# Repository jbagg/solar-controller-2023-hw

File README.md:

This is a differential temperature controller with 8 temperature sensor inputs, 4 digital inputs and 8 opto coupled solid state relay outputs.  The controller is compatible with the [LMT01](https://www.ti.com/product/LMT01) temperature sensor.  Each temperature sensor is connected to the controller with one pair of a cat 5 or 6 cable.  The temperature sensor uses the same 2 wires for both power and signaling.  Each temperature sensor has a max length of 45 meters.

The LMT01 is an ideal temperature sensor for differential temperature controllers as it

* uses digital signaling so no noise is added to the measurement over the cable back to the controller.
* allows for differential signaling for long cables.
* needs only 2 wires (twisted pair) per sensor.  Power and signaling is done over the same wires.

### Sensor Operation

The LMT01 uses a Pulse Train Interface to communicate the temperature where the number of output pulses is proportional to temperature.  The 1 or 0, high or low of each pulse is communicated by switching the device current consumption between two values, aprox 34uA and 125uA.

The controller measures each LMT01 sensor one at a time via U1, ADG707 differential 8-to-1 multiplexer.  When a sensor is muxed, its positive pin is connected to a 3.3kΩ pull up (R17) and its negative pin is connected to a 3.3kΩ pull down (R18).  Each resistor sees about a 300mV change in voltage between the pulse’s high / low 34uA and 125uA change in device current.  When R17’s change is positive, R18’s is negative.  These signal pulses are AC coupled to a differential op-amp circuit (U3A) via C20 and C39.  680pF was chosen to be about half the time constant for the 88Khz pulse.

1 / 88Khz = 11.4uS.  680pF * 10K = 6.8uS.

C20 and C39 must charge before they pass the pulses.  Too large a value looses pulses at the beginning.  680pF was measured to loose about 1 pulse, or about 0.1 C.

The differential op-amp circuit separates common noise from the differential signal that the twisted pair has picked up from noise sources over it’s length.  The differential op-amp circuit has gain to compensate for the signal loss in the cable.  The differential op-amp circuit has a gain of about 5 which is the max value not to saturate the strongest signal, a sensor connected directly to the controller without a length of wire.

[300mV - (-300mV)] * 5 <br>
= 600mV * 5 <br>
= 3v  (U1 has 3.3v supply)

The gain can be increased to just below the saturation point of the shortest cable.  C1 and C2 filter high frequency noise.  The output of the differential op-amp circuit is feed to a comparator with hysteresis (U3B).

The comparator has a hysteresis of 314mV.  A cat-5 twisted pair of up to 45 meters still had enough margin above the 314mV hysteresis for reliable operation.  The output of the comparator is feed to the microcontroller’s external timer counter clock input.

The microcontroller’s external timer counter clock (TCLK0) input feeds both TC0 and TC1 timer counters in the SAM4S2 mcu.  TC0 uses TCLK0 as a clock source and thus counts the pulses from the sensor.  The value of TC0 can be read and converted to a temperature.  TC1 is used to trigger when the LMT01 has finished sending pulses.  TC1 is clocked from the main mcu clock.  TC1 is configured so that its value is reset each time there is an edge on TCLK0.  TC1 compare C register is configured to a value about 2x the normal pulse period of the LMT01.  Each pulse from the LMT01 resets the count in TC1.  When the LMT01 stops sending pulses, TC1’s value grows to match compare C register which triggers an interrupt for the software to read TC0 and then change the mux to the next sensor and start all over again.

### Opto Coupler Ouptputs

Opto coupler AQH0213 is used to drive the coil of a relay that controls the load.  The AQH0213 is apart of a family of opto couplers with the same footprint.  The appropriate opto coupler can be chosen to match the voltage and current requirements of the specific relay for the application.

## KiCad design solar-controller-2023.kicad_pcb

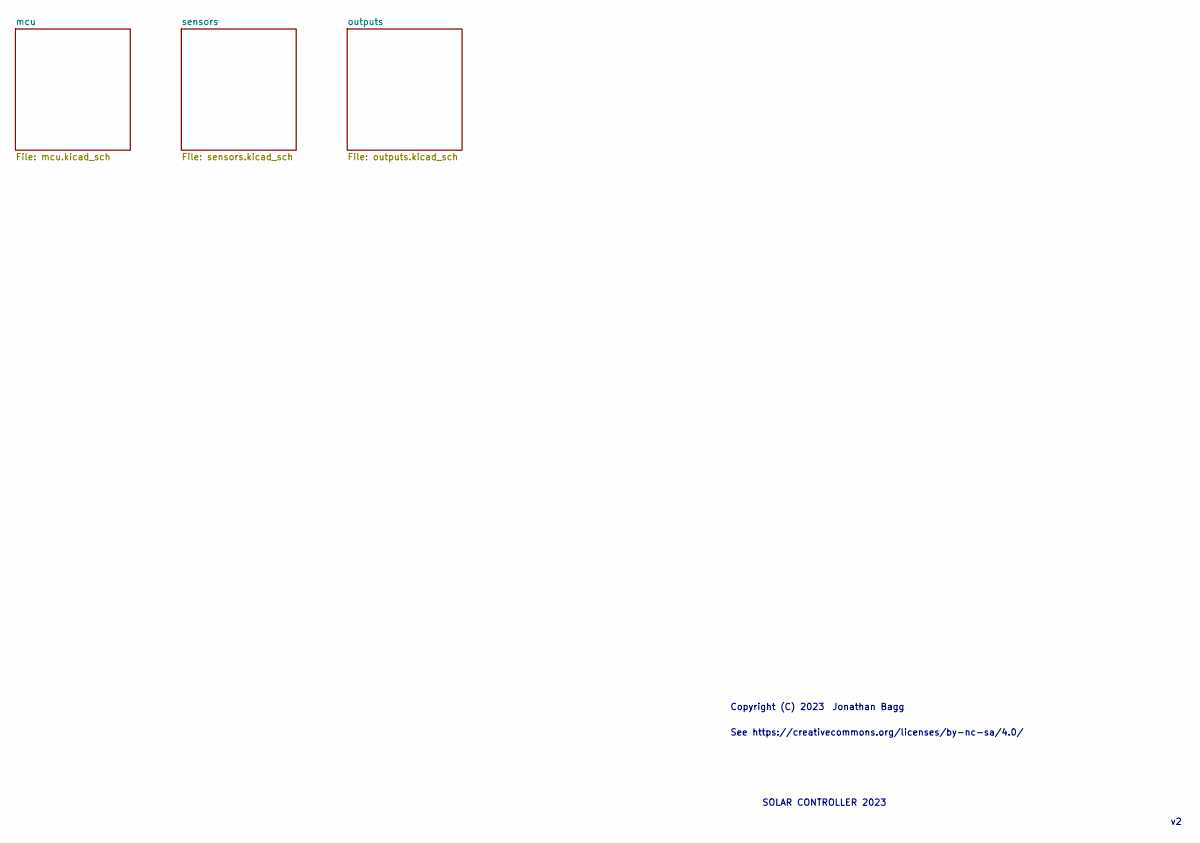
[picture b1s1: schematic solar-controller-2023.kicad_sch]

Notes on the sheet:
Copyright (C) 2023
See https://creativecommons.org/licenses/by-nc-sa/4.0/
Jonathan Bagg
SOLAR CONTROLLER 2023

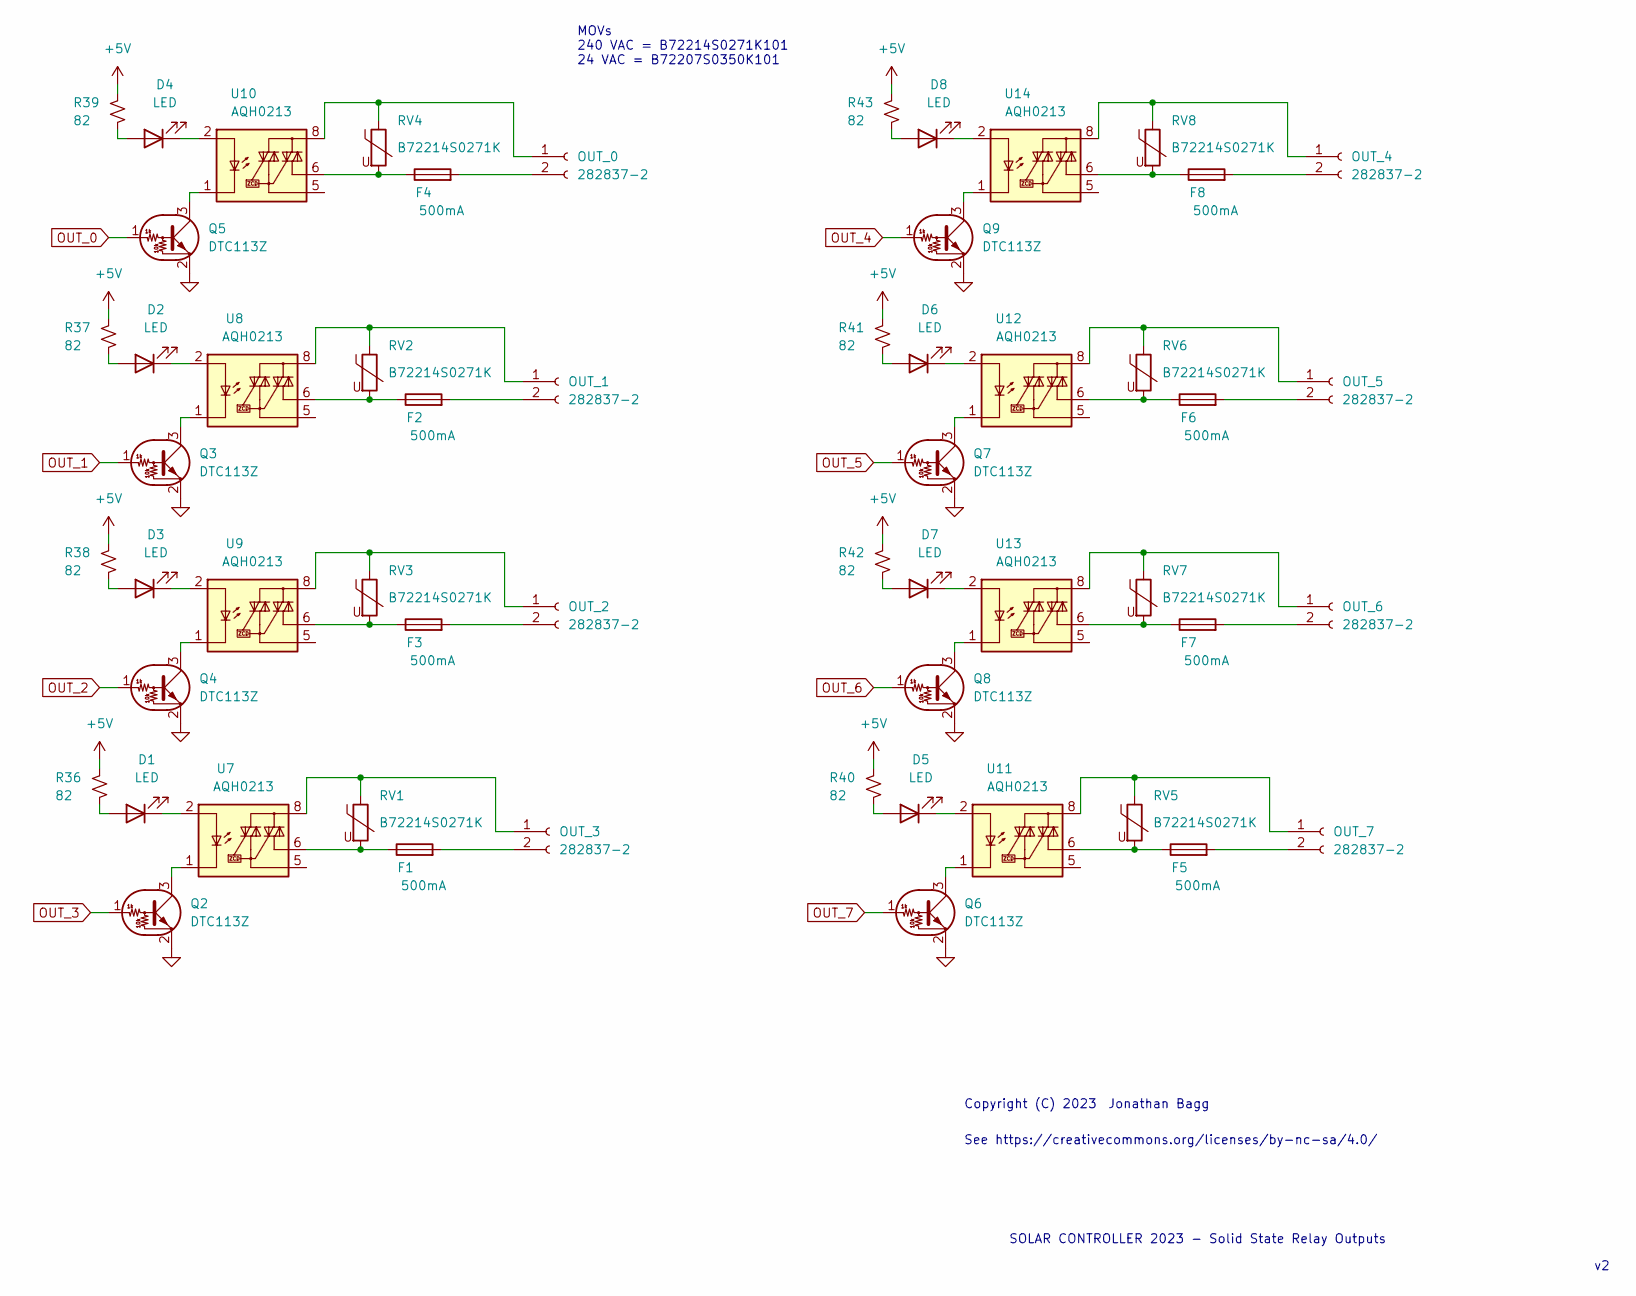
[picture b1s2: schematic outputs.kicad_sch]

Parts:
D1, D2, D3, D4, D5, D6, D7, D8: LED; D_0603_1608Metric_Pad1.05x0.95mm_HandSolder; Digikey 160-1436-1-ND
F1, F2, F3, F4, F5, F6, F7, F8: 500mA; C_Disc_D8.0mm_W5.0mm_P5.00mm; Digikey 507-1924-1-ND
OUT_0, OUT_1, OUT_2, OUT_3, OUT_4, OUT_5, OUT_6, OUT_7: 282837-2; 282837-2_TYC; Digikey A113320-ND
Q2, Q3, Q4, Q5, Q6, Q7, Q8, Q9: DTC113Z; SOT-23
R36, R37, R38, R39, R40, R41, R42, R43: 82; R_0805_2012Metric_Pad1.20x1.40mm_HandSolder; Digikey RMCF0805FT82R0CT-ND
RV1, RV2, RV3, RV4, RV5, RV6, RV7, RV8: B72214S0271K; C_Rect_L9.0mm_W2.5mm_P7.50mm_MKT; Digikey 495-1412-ND
U7, U8, U9, U10, U11, U12, U13, U14: AQH0213; DIP-8-N7_W7.62mm; Digikey 255-5987-ND

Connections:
+5V: R36.1, R37.1, R38.1, R39.1, R40.1, R41.1, R42.1, R43.1; also elsewhere on the board
GND: Q2.2 (E), Q3.2 (E), Q4.2 (E), Q5.2 (E), Q6.2 (E), Q7.2 (E), Q8.2 (E), Q9.2 (E); also elsewhere on the board
unnamed: D1.1 (K), U7.2
unnamed: D1.2 (A), R36.2
unnamed: D2.1 (K), U8.2
unnamed: D2.2 (A), R37.2
unnamed: D3.1 (K), U9.2
unnamed: D3.2 (A), R38.2
unnamed: D4.1 (K), U10.2
unnamed: D4.2 (A), R39.2
unnamed: D5.1 (K), U11.2
unnamed: D5.2 (A), R40.2
unnamed: D6.1 (K), U12.2
unnamed: D6.2 (A), R41.2
unnamed: D7.1 (K), U13.2
unnamed: D7.2 (A), R42.2
unnamed: D8.1 (K), U14.2
unnamed: D8.2 (A), R43.2
unnamed: F1.1, RV1.2, U7.6
unnamed: F1.2, OUT_3.2
unnamed: F2.1, RV2.2, U8.6
unnamed: F2.2, OUT_1.2
unnamed: F3.1, RV3.2, U9.6
unnamed: F3.2, OUT_2.2
unnamed: F4.1, RV4.2, U10.6
unnamed: F4.2, OUT_0.2
unnamed: F5.1, RV5.2, U11.6
unnamed: F5.2, OUT_7.2
unnamed: F6.1, RV6.2, U12.6
unnamed: F6.2, OUT_5.2
unnamed: F7.1, RV7.2, U13.6
unnamed: F7.2, OUT_6.2
unnamed: F8.1, RV8.2, U14.6
unnamed: F8.2, OUT_4.2
unnamed: OUT_0.1, RV4.1, U10.8
unnamed: OUT_1.1, RV2.1, U8.8
unnamed: OUT_2.1, RV3.1, U9.8
unnamed: OUT_3.1, RV1.1, U7.8
unnamed: OUT_4.1, RV8.1, U14.8
unnamed: OUT_5.1, RV6.1, U12.8
unnamed: OUT_6.1, RV7.1, U13.8
unnamed: OUT_7.1, RV5.1, U11.8
unnamed: Q2.3 (C), U7.1, U7.3, U7.4
unnamed: Q3.3 (C), U8.1, U8.3, U8.4
unnamed: Q4.3 (C), U9.1, U9.3, U9.4
unnamed: Q5.3 (C), U10.1, U10.3, U10.4
unnamed: Q6.3 (C), U11.1, U11.3, U11.4
unnamed: Q7.3 (C), U12.1, U12.3, U12.4
unnamed: Q8.3 (C), U13.1, U13.3, U13.4
unnamed: Q9.3 (C), U14.1, U14.3, U14.4
OUT_0: Q5.1 (B); also elsewhere on the board
OUT_1: Q3.1 (B); also elsewhere on the board
OUT_2: Q4.1 (B); also elsewhere on the board
OUT_3: Q2.1 (B); also elsewhere on the board
OUT_4: Q9.1 (B); also elsewhere on the board
OUT_5: Q7.1 (B); also elsewhere on the board
OUT_6: Q8.1 (B); also elsewhere on the board
OUT_7: Q6.1 (B); also elsewhere on the board

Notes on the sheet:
Copyright (C) 2023
See https://creativecommons.org/licenses/by-nc-sa/4.0/
MOVs 240 VAC = B72214S0271K101 24 VAC = B72207S0350K101
SOLAR CONTROLLER 2023 - Solid State Relay Outputs
Jonathan Bagg

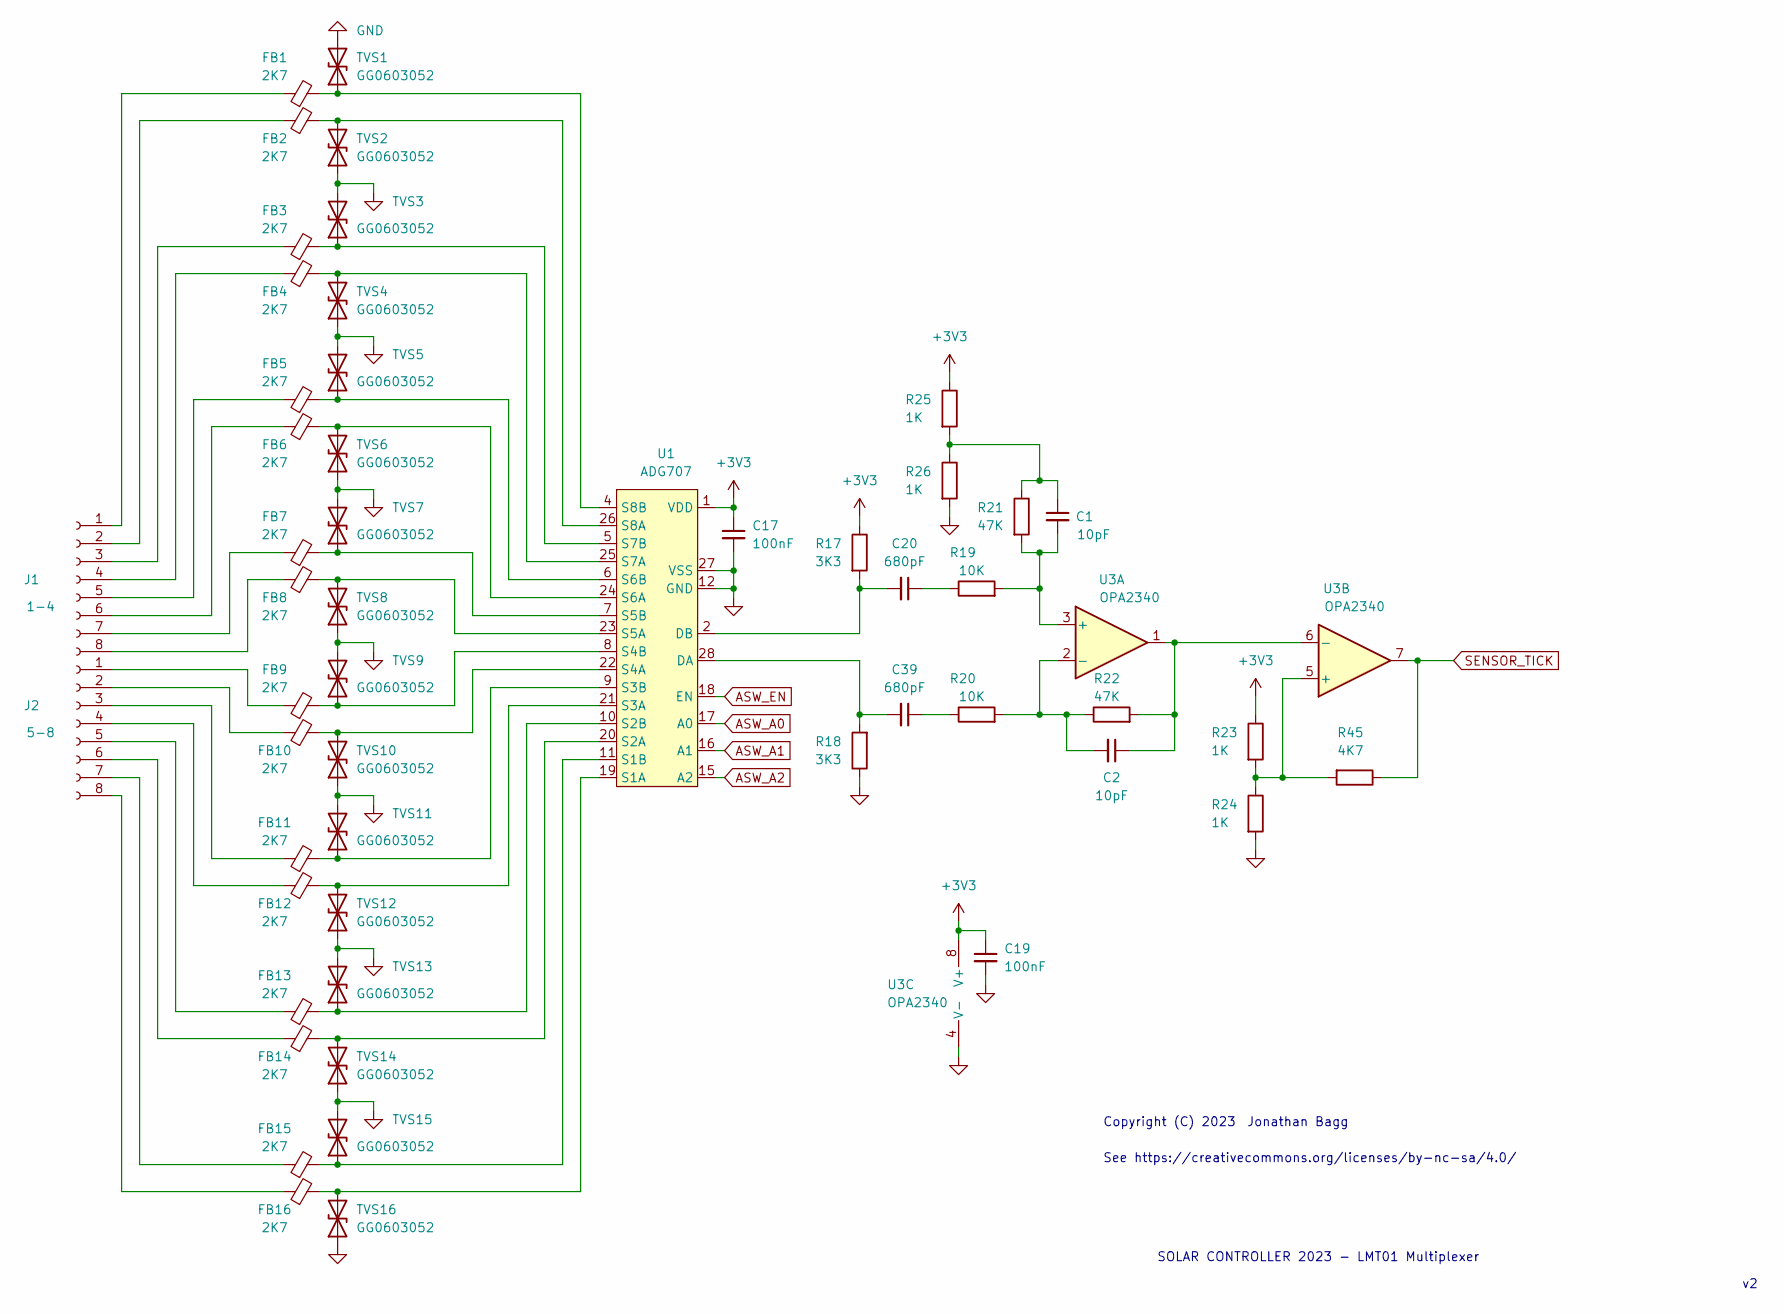
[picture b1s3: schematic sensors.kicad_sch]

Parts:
C1, C2: 10pF; C_0603_1608Metric_Pad1.08x0.95mm_HandSolder
C17, C19: 100nF; C_0603_1608Metric_Pad1.08x0.95mm_HandSolder
C20, C39: 680pF; C_0603_1608Metric_Pad1.08x0.95mm_HandSolder
FB1, FB2, FB3, FB4, FB5, FB6, FB7, FB8, FB9, FB10, FB11, FB12, FB13, FB14, FB15, FB16: 2K7; C_0603_1608Metric_Pad1.08x0.95mm_HandSolder
J1: 1-4; PinHeader_1x08_P2.54mm_Vertical; Digikey A98338-ND
J2: 5-8; PinHeader_1x08_P2.54mm_Vertical; Digikey A98338-ND
R17, R18: 3K3; R_0603_1608Metric_Pad0.98x0.95mm_HandSolder
R19, R20: 10K; R_0603_1608Metric_Pad0.98x0.95mm_HandSolder
R21, R22: 47K; R_0603_1608Metric_Pad0.98x0.95mm_HandSolder
R23, R24, R25, R26: 1K; R_0603_1608Metric_Pad0.98x0.95mm_HandSolder
R45: 4K7; R_0603_1608Metric_Pad0.98x0.95mm_HandSolder
TVS1, TVS2, TVS3, TVS4, TVS5, TVS6, TVS7, TVS8, TVS9, TVS10, TVS11, TVS12, TVS13, TVS14, TVS15, TVS16: GG0603052; D_0603_1608Metric_Pad1.05x0.95mm_HandSolder; Digikey 478-GG0603052R542PCT-ND
U1: ADG707; SSOP-28_5.3x10.2mm_P0.65mm
U3: OPA2340; SOP-8_3.9x4.9mm_P1.27mm; Digikey 296-26253-1-ND

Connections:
+3V3: C17.1, C19.1, R17.1, R23.1, R25.1, U1.1 (VDD), U3.8 (V+); also elsewhere on the board
ASW_A0: U1.17 (A0); also elsewhere on the board
ASW_A1: U1.16 (A1); also elsewhere on the board
ASW_A2: U1.15 (A2); also elsewhere on the board
ASW_EN: U1.18 (EN); also elsewhere on the board
GND: C17.2, C19.2, R18.1, R24.2, R26.2, TVS1.2 (A2), TVS2.1 (A1), TVS3.2 (A2), TVS4.1 (A1), TVS5.2 (A2), TVS6.1 (A1), TVS7.2 (A2), TVS8.1 (A1), TVS9.2 (A2), TVS10.1 (A1), TVS11.2 (A2), TVS12.1 (A1), TVS13.2 (A2), TVS14.1 (A1), TVS15.2 (A2), TVS16.1 (A1), U1.12 (GND), U1.27 (VSS), U3.4 (V-); also elsewhere on the board
unnamed: C20.1, R19.1
unnamed: C39.1, R20.1
unnamed: FB1.1, J1.1
unnamed: FB1.2, TVS1.1 (A1), U1.4 (S8B)
unnamed: FB2.1, J1.2
unnamed: FB2.2, TVS2.2 (A2), U1.26 (S8A)
unnamed: FB3.1, J1.3
unnamed: FB3.2, TVS3.1 (A1), U1.5 (S7B)
unnamed: FB4.1, J1.4
unnamed: FB4.2, TVS4.2 (A2), U1.25 (S7A)
unnamed: FB5.1, J1.5
unnamed: FB5.2, TVS5.1 (A1), U1.6 (S6B)
unnamed: FB6.1, J1.6
unnamed: FB6.2, TVS6.2 (A2), U1.24 (S6A)
unnamed: FB7.1, J1.7
unnamed: FB7.2, TVS7.1 (A1), U1.7 (S5B)
unnamed: FB8.1, J1.8
unnamed: FB8.2, TVS8.2 (A2), U1.23 (S5A)
unnamed: FB9.1, J2.1
unnamed: FB9.2, TVS9.1 (A1), U1.8 (S4B)
unnamed: FB10.1, J2.2
unnamed: FB10.2, TVS10.2 (A2), U1.22 (S4A)
unnamed: FB11.1, J2.3
unnamed: FB11.2, TVS11.1 (A1), U1.9 (S3B)
unnamed: FB12.1, J2.4
unnamed: FB12.2, TVS12.2 (A2), U1.21 (S3A)
unnamed: FB13.1, J2.5
unnamed: FB13.2, TVS13.1 (A1), U1.10 (S2B)
unnamed: FB14.1, J2.6
unnamed: FB14.2, TVS14.2 (A2), U1.20 (S2A)
unnamed: FB15.1, J2.7
unnamed: FB15.2, TVS15.1 (A1), U1.11 (S1B)
unnamed: FB16.1, J2.8
unnamed: FB16.2, TVS16.2 (A2), U1.19 (S1A)
unnamed: C20.2, R17.2, U1.2 (DB)
unnamed: C39.2, R18.2, U1.28 (DA)
unnamed: C1.2, R19.2, R21.2, U3.3 (+)
unnamed: C2.2, R20.2, R22.1, U3.2 (-)
unnamed: C2.1, R22.2, U3.1, U3.6 (-)
unnamed: R23.2, R24.1, R45.2, U3.5 (+)
unnamed: C1.1, R21.1, R25.2, R26.1
SENSOR_TICK: R45.1, U3.7; also elsewhere on the board

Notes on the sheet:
See https://creativecommons.org/licenses/by-nc-sa/4.0/
Copyright (C) 2023
SOLAR CONTROLLER 2023 - LMT01 Multiplexer
Jonathan Bagg

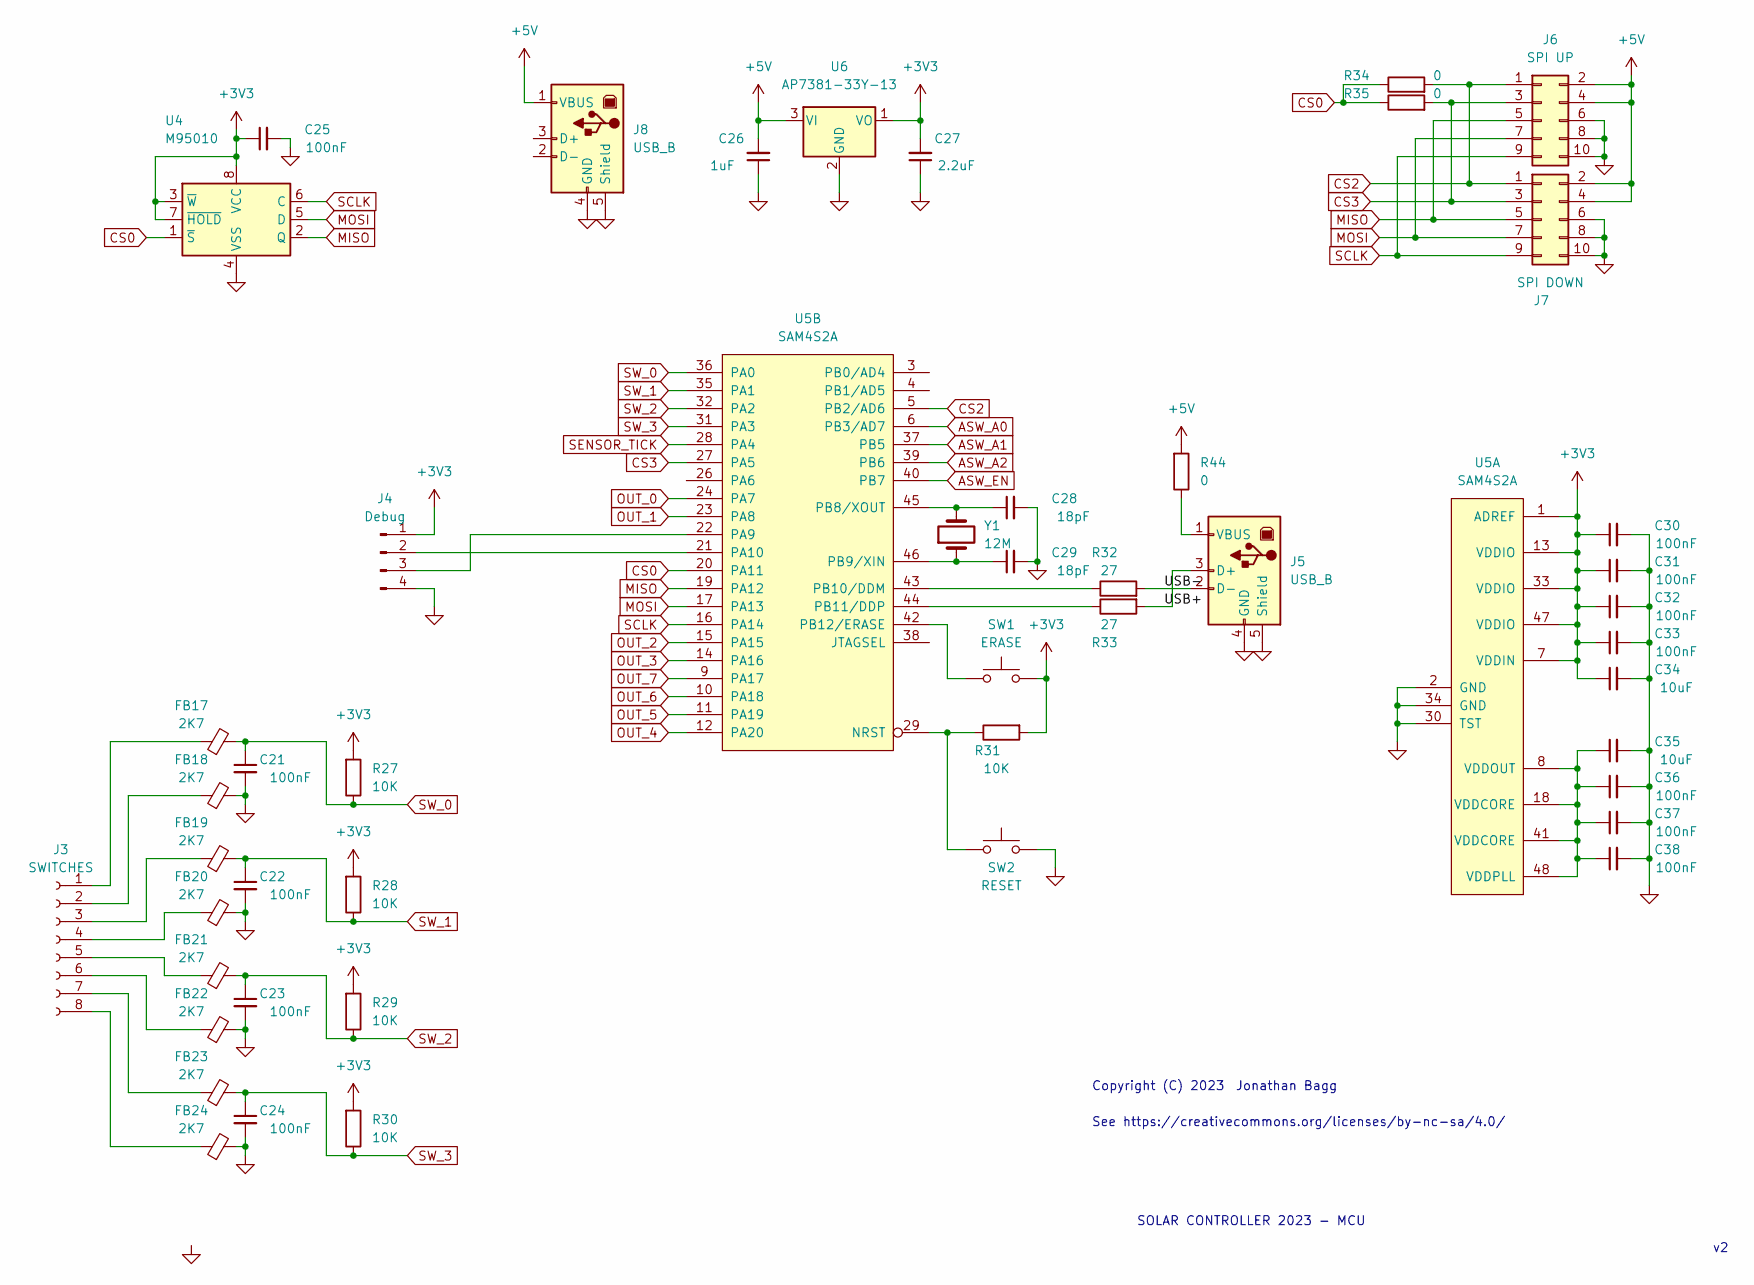
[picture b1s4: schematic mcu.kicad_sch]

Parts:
C21, C22, C23, C24, C25, C30, C31, C32, C33, C36, C37, C38: 100nF; C_0603_1608Metric_Pad1.08x0.95mm_HandSolder
C26: 1uF; C_0805_2012Metric_Pad1.18x1.45mm_HandSolder; Digikey 490-10494-1-ND
C27: 2.2uF; C_0805_2012Metric_Pad1.18x1.45mm_HandSolder; Digikey 587-EMF212B7225KGHTCT-ND
C28, C29: 18pF; C_0603_1608Metric_Pad1.08x0.95mm_HandSolder
C34, C35: 10uF; C_0805_2012Metric_Pad1.18x1.45mm_HandSolder
FB17, FB18, FB19, FB20, FB21, FB22, FB23, FB24: 2K7; C_0603_1608Metric_Pad1.08x0.95mm_HandSolder
J3: SWITCHES; PinHeader_1x08_P2.54mm_Vertical; Digikey A98338-ND
J4: Debug; PinHeader_1x04_P2.54mm_Vertical
J5, J8: USB_B; USB_Micro-B_Amphenol_10118194_Horizontal; Digikey 609-4618-1-ND
J6: SPI UP; PinHeader_2x05_P2.54mm_Vertical; Digikey 732-2865-ND
J7: SPI DOWN; PinHeader_2x05_P2.54mm_Vertical; Digikey 732-2676-ND
R27, R28, R29, R30, R31: 10K; R_0603_1608Metric_Pad0.98x0.95mm_HandSolder
R32, R33: 27; R_0603_1608Metric_Pad0.98x0.95mm_HandSolder
R34, R35, R44: 0; R_0603_1608Metric_Pad0.98x0.95mm_HandSolder
SW1: ERASE; SW_Push_1P1T_NO_6x6mm_H9.5mm; Digikey 2223-TS04-66-50-BK-260-SMT-ND
SW2: RESET; SW_Push_1P1T_NO_6x6mm_H9.5mm; Digikey 2223-TS04-66-50-BK-260-SMT-ND
U4: M95010; SOIC-8_3.9x4.9mm_P1.27mm; Digikey 497-8672-1-ND
U5: SAM4S2A; LQFP-48_7x7mm_P0.5mm; Digikey ATSAM4S2AB-ANR-CT-ND
U6: AP7381-33Y-13; SOT-89-3-JB; Digikey AP7381-33Y-13DICT-ND
Y1: 12M; Crystal_HC49-4H_Vertical

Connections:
+3V3: C25.1, C27.2, C30.1, C31.1, C32.1, C33.1, C34.1, J4.1, R27.2, R28.2, R29.2, R30.2, R31.2, SW1.2, U4.3 (~W), U4.7 (~HOLD), U4.8 (VCC), U5.1 (ADREF), U5.7 (VDDIN), U5.13 (VDDIO), U5.33 (VDDIO), U5.47 (VDDIO), U6.1 (VO); also elsewhere on the board
+5V: C26.2, J6.2, J6.4, J7.2, J7.4, J8.1 (VBUS), R44.2, U6.3 (VI); also elsewhere on the board
/mcu/USB+: J5.3 (D+), R33.2
/mcu/USB-: J5.2 (D-), R32.2
ASW_A0: U5.6 (PB3/AD7); also elsewhere on the board
ASW_A1: U5.37 (PB5); also elsewhere on the board
ASW_A2: U5.39 (PB6); also elsewhere on the board
ASW_EN: U5.40 (PB7); also elsewhere on the board
CS0: R34.1, R35.1, U4.1 (~S), U5.20 (PA11)
CS2: J6.1, J7.1, R34.2, U5.5 (PB2/AD6)
CS3: J6.3, J7.3, R35.2, U5.27 (PA5)
GND: C21.2, C22.2, C23.2, C24.2, C25.2, C26.1, C27.1, C28.2, C29.2, C30.2, C31.2, C32.2, C33.2, C34.2, C35.2, C36.2, C37.2, C38.2, FB18.2, FB20.2, FB22.2, FB24.2, J4.4, J5.4 (GND), J5.5 (Shield), J6.6, J6.8, J6.10, J7.6, J7.8, J7.10, J8.4 (GND), J8.5 (Shield), SW2.2, U4.4 (VSS), U5.2 (GND), U5.30 (TST), U5.34 (GND), U6.2 (GND); also elsewhere on the board
MISO: J6.5, J7.5, U4.2 (Q), U5.19 (PA12)
MOSI: J6.7, J7.7, U4.5 (D), U5.17 (PA13)
unnamed: C28.1, U5.45 (PB8/XOUT), Y1.2
unnamed: C29.1, U5.46 (PB9/XIN), Y1.1
unnamed: C35.1, C36.1, C37.1, C38.1, U5.8 (VDDOUT), U5.18 (VDDCORE), U5.41 (VDDCORE), U5.48 (VDDPLL)
unnamed: FB17.1, J3.1
unnamed: FB18.1, J3.2
unnamed: FB19.1, J3.3
unnamed: FB20.1, J3.4
unnamed: FB21.1, J3.5
unnamed: FB22.1, J3.6
unnamed: FB23.1, J3.7
unnamed: FB24.1, J3.8
unnamed: J4.2, U5.21 (PA10)
unnamed: J4.3, U5.22 (PA9)
unnamed: J5.1 (VBUS), R44.1
unnamed: R31.1, SW2.1, U5.29 (NRST)
unnamed: R32.1, U5.43 (PB10/DDM)
unnamed: R33.1, U5.44 (PB11/DDP)
unnamed: SW1.1, U5.42 (PB12/ERASE)
OUT_0: U5.24 (PA7); also elsewhere on the board
OUT_1: U5.23 (PA8); also elsewhere on the board
OUT_2: U5.15 (PA15); also elsewhere on the board
OUT_3: U5.14 (PA16); also elsewhere on the board
OUT_4: U5.12 (PA20); also elsewhere on the board
OUT_5: U5.11 (PA19); also elsewhere on the board
OUT_6: U5.10 (PA18); also elsewhere on the board
OUT_7: U5.9 (PA17); also elsewhere on the board
SCLK: J6.9, J7.9, U4.6 (C), U5.16 (PA14)
SENSOR_TICK: U5.28 (PA4); also elsewhere on the board
SW_0: C21.1, FB17.2, R27.1, U5.36 (PA0)
SW_1: C22.1, FB19.2, R28.1, U5.35 (PA1)
SW_2: C23.1, FB21.2, R29.1, U5.32 (PA2)
SW_3: C24.1, FB23.2, R30.1, U5.31 (PA3)

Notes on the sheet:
See https://creativecommons.org/licenses/by-nc-sa/4.0/
Jonathan Bagg
SOLAR CONTROLLER 2023 - MCU
Copyright (C) 2023

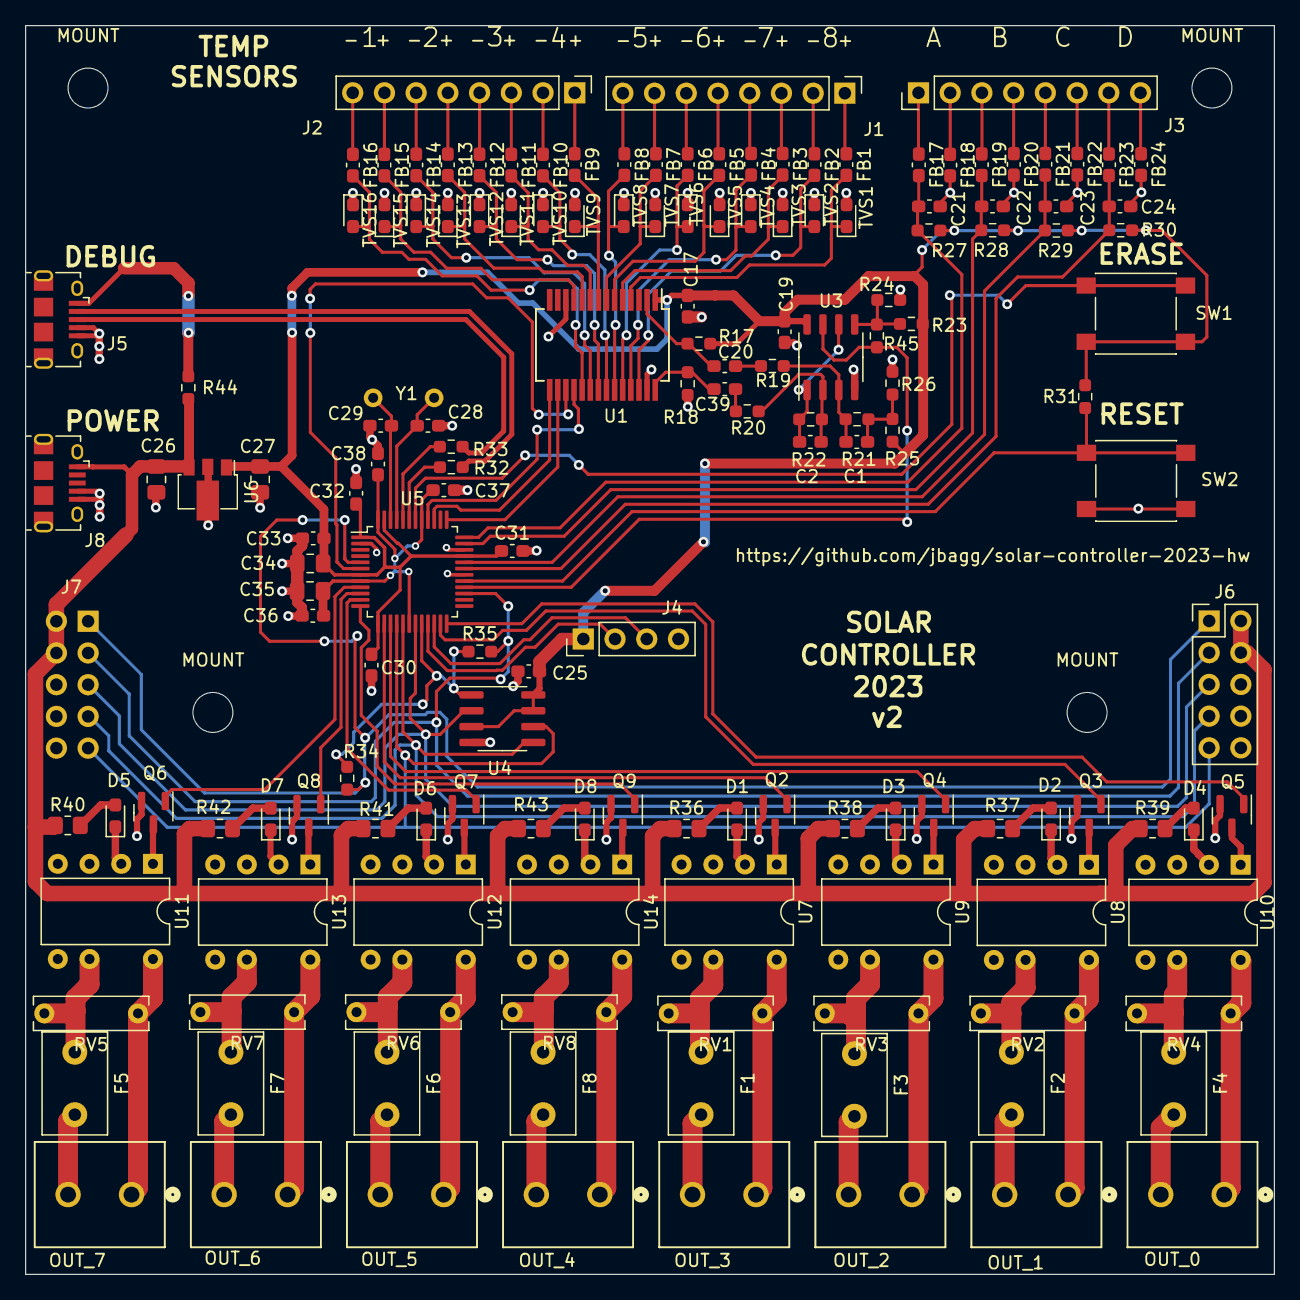
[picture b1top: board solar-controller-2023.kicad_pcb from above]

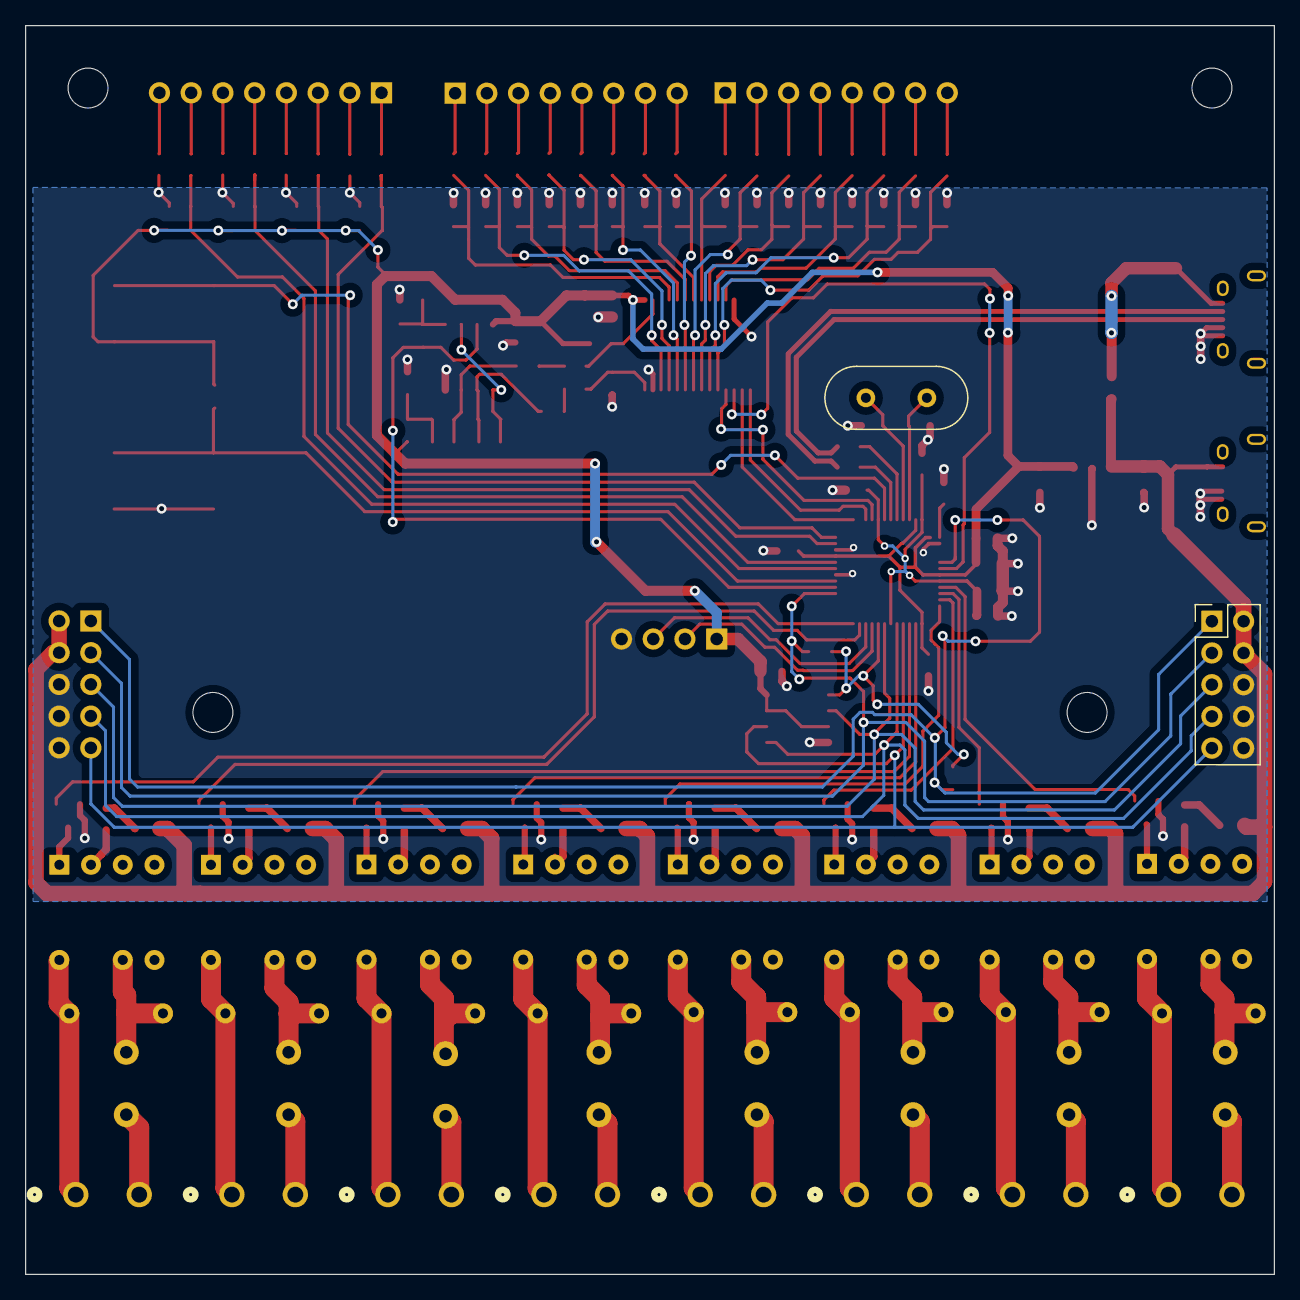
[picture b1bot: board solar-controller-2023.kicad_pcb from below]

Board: 2 copper layers, 100.0 x 100.0 mm, 161 parts (2 on the bottom side), 135 nets.

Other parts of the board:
MOUNT: MountingHole_3.2mm_M3
MOUNT#2, MOUNT#3, MOUNT#4: MountingHole_3.2mm_M3

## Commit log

2023-10-07 schematic annotated
2023-10-10 changes for layout
2023-10-10 add gerbers
2023-10-11 should have been committed before gerber generation
2023-10-11 added some part numbers
2023-11-05 add copyright notices
2023-11-05 add pdf of schematic
2023-11-06 AC couple LMT01 signal conditioning and add gain
    The difference circuit U3A was DC coupled and so could not
    have gain. Unit gain was only good for sensors up to 15m of
    cat-5.
2023-11-08 replace sensor wire esd caps with TVSs
2023-11-15 generate gerbers
2023-11-15 add github link to title block and print schematic pdf
2023-12-03 adding README
